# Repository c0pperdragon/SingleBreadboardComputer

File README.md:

# SingleBreadboardComputer
A 65C02-based computer squeezed onto a single breadboard.

## The Challenge
Designs for SBCs based on the 6502 are quit common, but normally they use
some specialized ICs to handle the IO. I did some designs myself using 
standard 74-logic for the auxilary functionality.

Pushing the minimalist approach to the extreme, I decided to find a way 
to fit a 65C02-based computer into 5 ICs including oscillator, CPU, RAM and ROM.
To consider the system complete, it would have to meet the following 
specs:
* 65C02 CPU @10MHz
* 32K FLASH
* 32K RAM
* Software-driven I/O

## Space constraints
The BB630 board is big enough to fit the mandatory CPU/RAM/FLASH ICs and one 
additional small IC. This additional IC has to somehow implement all he
necessary logic for both the memory addressing as well as for the IO.
A quad 2-input NAND (74HC00) is a pretty versatile option here.
Some very narrow spaces between these ICs can be used for a bit of 
analog circuitry.

## Clock generator
Without dedicated space to fit the osciallator, I came up with the solution
to place it partly on the power rail. This is possible because it only has 
4 pins of which one is not even connected inside my specific part.

## Address logic
As it turns out, it is enough to use only 2 NANDs to drive the 
RAM and the FLASH in a rather unusual way. One side effect of this 
implementation is that the access time for the RAM is reduced to
only half a clock cycle, so I use an extra fast RAM here (12ns access time).

## Serial input
Receiving incoming data can be done purely in software when using the IRQB
pin of the CPU. It requires some serious cycle-counting in implementing the 
software, but It can be done somehow.

Unluckily, the SOB input pin is only edge-triggered and is unsuitable to 
implement a regular serial protocol.

## Serial output
This CPU provides the MLB pin that is intended to implement 
multi-processor systems. By using some specific CPU instructions 
(all with a read-modify-write functionality), this pin can be driven low for 
2 clock cycles at a time. 
While this is not enough to directly implement a serial output, it is one part of the 
solution. 

The other part is to use the two unused NAND-gates to implement an RS-flipflop which has
the MLB pin as its R input and the A15 address line as its S input.

The overall result of this circuit is that the CPU can drive the flipflop to its low 
state by executing one of the read-modify-write instructions on a ROM address.
And it can drive it high again by doing any access to the RAM. 
This is enough to drive a serial output signal in software

## Proof-of-concept software
I don't intend to do much more programming on this device, but I have implemented
a simple demonstration of the IO possibilities. It writes a short message to the
output and then waits for incoming bytes, which it will then write in hex digits
back to the output.

Communication is done with 115200 baud, one start bit, one stop bit.

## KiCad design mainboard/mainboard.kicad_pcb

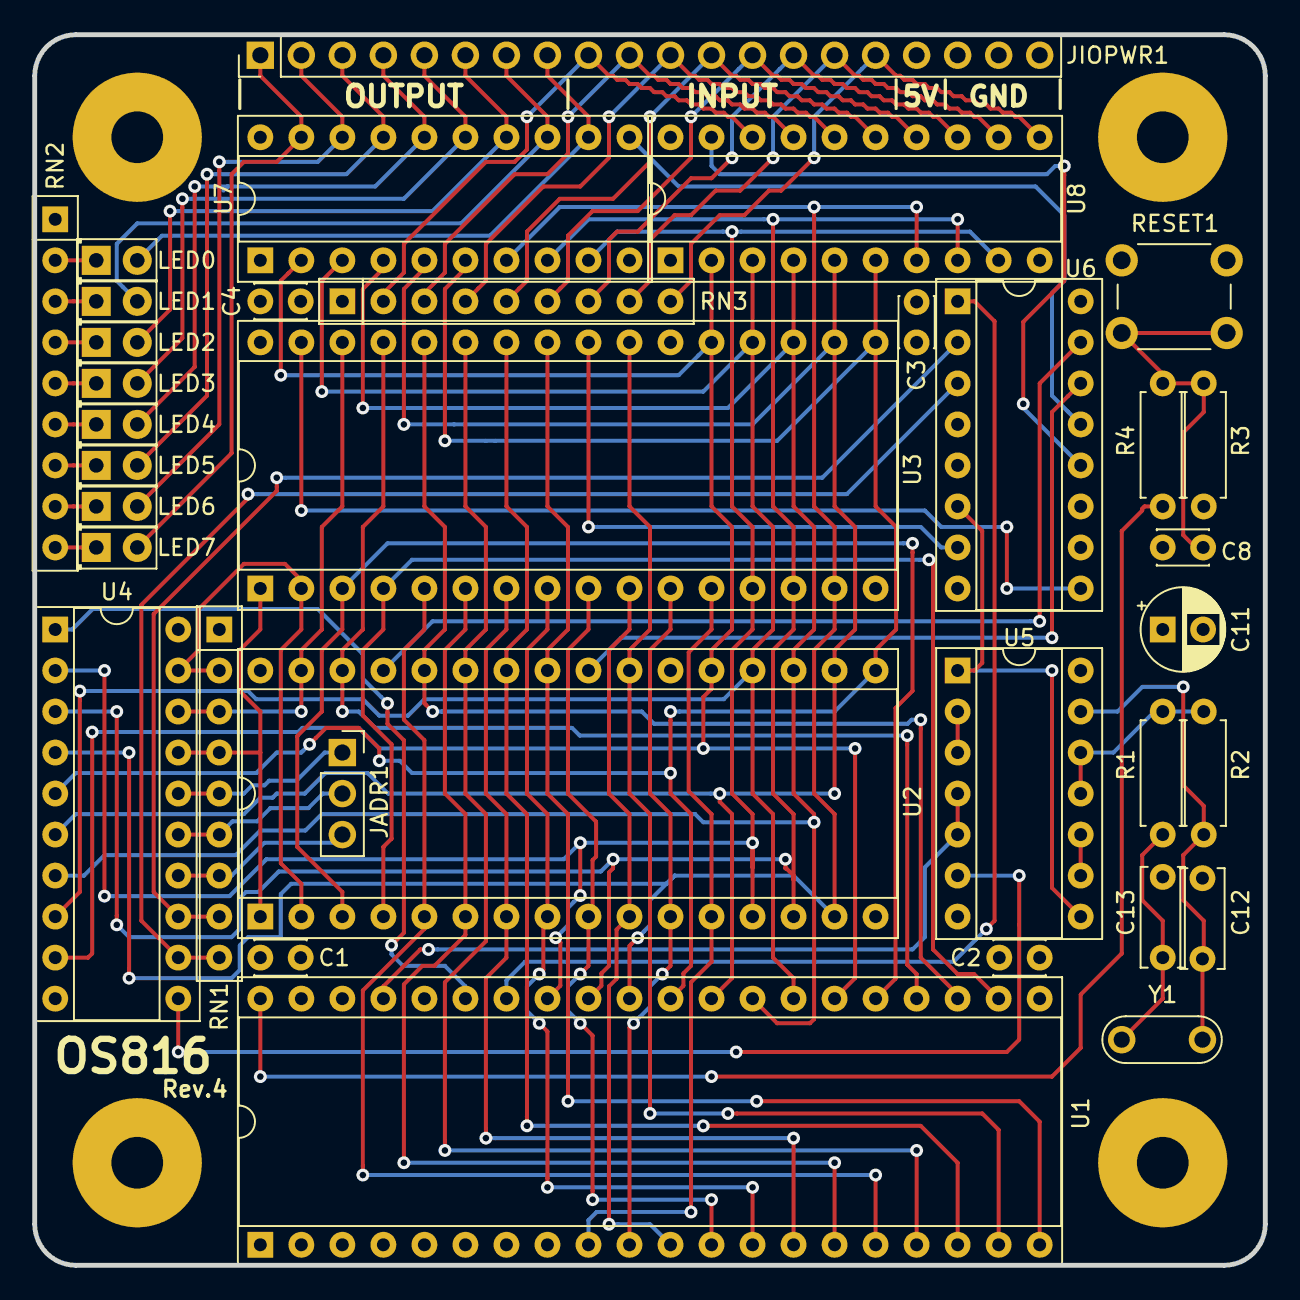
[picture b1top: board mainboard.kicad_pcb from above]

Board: 4 copper layers, 76.2 x 76.2 mm, 35 parts (0 on the bottom side), 76 nets.

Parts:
C1, C2, C3, C4: 100nF; C_Disc_D3.0mm_W2.0mm_P2.50mm
C8: 1uF; C_Disc_D3.0mm_W2.0mm_P2.50mm
C11: 100uF; CP_Radial_D5.0mm_P2.50mm
C12, C13: 33pF; C_Disc_D6.0mm_W2.5mm_P5.00mm
JADR1: Conn_01x03; PinSocket_1x03_P2.54mm_Vertical
JIOPWR1: Conn_01x20_Male; PinHeader_1x20_P2.54mm_Vertical
LED0, LED1, LED2, LED3, LED4, LED5, LED6, LED7: LED_Small; LED_D2.0mm_W4.8mm_H2.5mm_FlatTop
R1: 1k; R_Axial_DIN0207_L6.3mm_D2.5mm_P7.62mm_Horizontal
R2: 1M; R_Axial_DIN0207_L6.3mm_D2.5mm_P7.62mm_Horizontal
R3, R4: 10k; R_Axial_DIN0207_L6.3mm_D2.5mm_P7.62mm_Horizontal
RESET1: SW_Push; SW_PUSH_6mm_H4.3mm
RN1, RN3: 10k; R_Array_SIP9
RN2: 1k; R_Array_SIP9
U1: 65C816; DIP-40_W15.24mm_Socket
U2: AS6C4008; DIP-32_W15.24mm_Socket
U3: SST39SF040; DIP-32_W15.24mm_Socket
U4: 74AC573; DIP-20_W7.62mm_Socket
U5: 74HC04; DIP-14_W7.62mm_Socket
U6: 74HC138; DIP-16_W7.62mm_Socket
U7: 74HC574; DIP-20_W7.62mm_Socket
U8: 74HC245; DIP-20_W7.62mm_Socket
Y1: 10MHz; Resonator-2Pin_W7.0mm_H2.5mm

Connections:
+5V: C1.1, C2.1, C3.1, C4.1, C11.1, JIOPWR1.17, R3.1, RN1.1, RN3.1, U1.3, U1.4, U1.6, U1.8, U1.36, U2.32, U3.32, U4.20, U5.14, U6.16, U7.20, U8.20
/A0: U1.9, U2.12, U3.12
/A1: U1.10, U2.11, U3.11
/A2: U1.11, U2.10, U3.10
/A3: U1.12, U2.9, U3.9
/A4: U1.13, U2.8, U3.8
/A5: U1.14, U2.7, U3.7
/A6: U1.15, U2.6, U3.6
/A7: U1.16, U2.5, U3.5
/A8: U1.17, U2.27, U3.27
/A9: U1.18, U2.26, U3.26
/A10: U1.19, U2.23, U3.23
/A11: U1.20, U2.25, U3.25
/A12: U1.22, U2.4, U3.4
/A13: U1.23, U2.28, U3.28
/A14: U1.24, U2.30, U3.29
/A15: U1.25, U2.3, U3.3
/A16: RN1.2, U2.2, U3.2, U4.19
/A17: RN1.3, U2.31, U3.30, U4.18
/A18: RN1.4, U2.1, U3.1, U4.17
/A19: JADR1.1, RN1.5, U4.16
/A20: JADR1.2, RN1.6, U4.15
/A21: JADR1.3, RN1.7, U4.14
/A22: RN1.8, U4.13, U6.2
/A23: RN1.9, U4.12, U6.3
/CLK: U1.37, U5.4, U5.5
/CLK#: U4.11, U5.6
/CLKFAST: U5.1, U5.8, U6.6
/D0: U1.33, U2.13, U3.13, U4.2, U7.9, U8.9
/D1: U1.32, U2.14, U3.14, U4.3, U7.8, U8.8
/D2: U1.31, U2.15, U3.15, U4.4, U7.7, U8.7
/D3: U1.30, U2.17, U3.17, U4.5, U7.6, U8.6
/D4: U1.29, U2.18, U3.18, U4.6, U7.5, U8.5
/D5: U1.28, U2.19, U3.19, U4.7, U7.4, U8.4
/D6: U1.27, U2.20, U3.20, U4.8, U7.3, U8.3
/D7: U1.26, U2.21, U3.21, U4.9, U7.2, U8.2
/E: U1.35, U4.1
/FLASHRD#: U3.24, U6.7
/FLASHWR#: U3.31, U6.9
/IN0: JIOPWR1.16, RN3.9, U8.11
/IN1: JIOPWR1.15, RN3.8, U8.12
/IN2: JIOPWR1.14, RN3.7, U8.13
/IN3: JIOPWR1.13, RN3.6, U8.14
/IN4: JIOPWR1.12, RN3.5, U8.15
/IN5: JIOPWR1.11, RN3.4, U8.16
/IN6: JIOPWR1.10, RN3.3, U8.17
/IN7: JIOPWR1.9, RN3.2, U8.18
/IORD#: U6.12, U8.19
/IOWR#: U6.13, U7.11
/OUT0: JIOPWR1.8, LED0.2, U7.12
/OUT1: JIOPWR1.7, LED1.2, U7.13
/OUT2: JIOPWR1.6, LED2.2, U7.14
/OUT3: JIOPWR1.5, LED3.2, U7.15
/OUT4: JIOPWR1.4, LED4.2, U7.16
/OUT5: JIOPWR1.3, LED5.2, U7.17
/OUT6: JIOPWR1.2, LED6.2, U7.18
/OUT7: JIOPWR1.1, LED7.2, U7.19
/RAMRD#: U2.24, U6.14
/RAMWR#: U2.29, U6.15
/RES: R4.1, U1.40
/RWB: U1.34, U6.1
GND: C1.2, C2.2, C3.2, C4.2, C8.1, C11.2, C12.2, C13.2, JIOPWR1.18, JIOPWR1.19, JIOPWR1.20, RESET1.1, RN2.1, U1.21, U2.16, U2.22, U3.16, U3.22, U4.10, U5.7, U6.4, U6.5, U6.8, U7.1, U7.10, U8.1, U8.10
unnamed: C8.2, R3.2, R4.2, RESET1.2
unnamed: C12.1, R2.1, U5.13, Y1.1
unnamed: C13.1, R1.2, Y1.2
unnamed: LED0.1, RN2.2
unnamed: LED1.1, RN2.3
unnamed: LED2.1, RN2.4
unnamed: LED3.1, RN2.5
unnamed: LED4.1, RN2.6
unnamed: LED5.1, RN2.7
unnamed: LED6.1, RN2.8
unnamed: LED7.1, RN2.9
unnamed: R1.1, R2.2, U5.11, U5.12
unnamed: U5.2, U5.3
unnamed: U5.9, U5.10

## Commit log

2022-11-09 Boot assembly code
2022-11-10 Firmware development
2022-11-11 Read input pin
2022-11-13 Implement data read from serial
2022-11-15 More IO functions
2022-11-17 Schematic
2022-11-17 Fixes in schematic
2022-11-18 Upload image
2022-11-19 Docu
2022-11-19 Typos
2022-11-19 Include executable binary
2022-11-24 Fix spelling for 'coming'

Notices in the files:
mainboard/mainboard.kicad_pcb:
github.com/c0pperdragon/OS816  © 2021 Reinhard Grafl
